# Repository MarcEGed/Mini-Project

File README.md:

# FELCOM

FELCOM is a secure handheld communication device built around the ESP32 and nRF24L01+. The firmware supports frequency-hopping communication, text chat, voice, synchronization, and RF testing.

## Repository layout

- [`FELCOM/`](FELCOM/) - PlatformIO firmware project.
- [`hardware/`](hardware/) - KiCad PCB design, fabrication outputs, and hardware images.
- [`docs/`](docs/) - Project notes, report sources and deliverables, diagrams, and hardware documentation.
- [`miscExperimenting/`](miscExperimenting/) - Earlier Arduino sketches and communication experiments.
- [`template/`](template/) - Typst report template and license.

## Documentation

- [`docs/felcom/AUDIO.md`](docs/felcom/AUDIO.md) - Audio pipeline, wiring, FEC behavior, and troubleshooting.
- [`docs/felcom/fhss.md`](docs/felcom/fhss.md) - FHSS channels, packet format, and synchronization design.
- [`docs/hardware/README.md`](docs/hardware/README.md) - Circuit assembly references.
- [`docs/report/`](docs/report/) - Typst report source, PDF report, and presentation.
- [`docs/diagrams/`](docs/diagrams/) - Mermaid source files and rendered report diagrams.

## Build and upload

Install PlatformIO, connect an ESP32 development board, and run the commands from `FELCOM/`:

```sh
pio run -e esp32dev
pio run -e esp32dev -t upload
```

The two communicating boards must run the same firmware. Use the Sync Test screen to synchronize their hopping schedule before using chat or audio.

## Hardware

The main hardware design is in [`hardware/fabrication_pcb/`](hardware/fabrication_pcb/). Consult the hardware documentation before assembling a board. Pin assignments and firmware configuration are in [`FELCOM/include/config.h`](FELCOM/include/config.h).

## Report

The current report and presentation are available in [`docs/report/`](docs/report/). The report source is compiled with Typst and uses the diagrams in [`docs/diagrams/`](docs/diagrams/) and images in [`hardware/imgs/`](hardware/imgs/).

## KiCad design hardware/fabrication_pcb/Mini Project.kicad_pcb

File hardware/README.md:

# Reference For Circuit Assembly

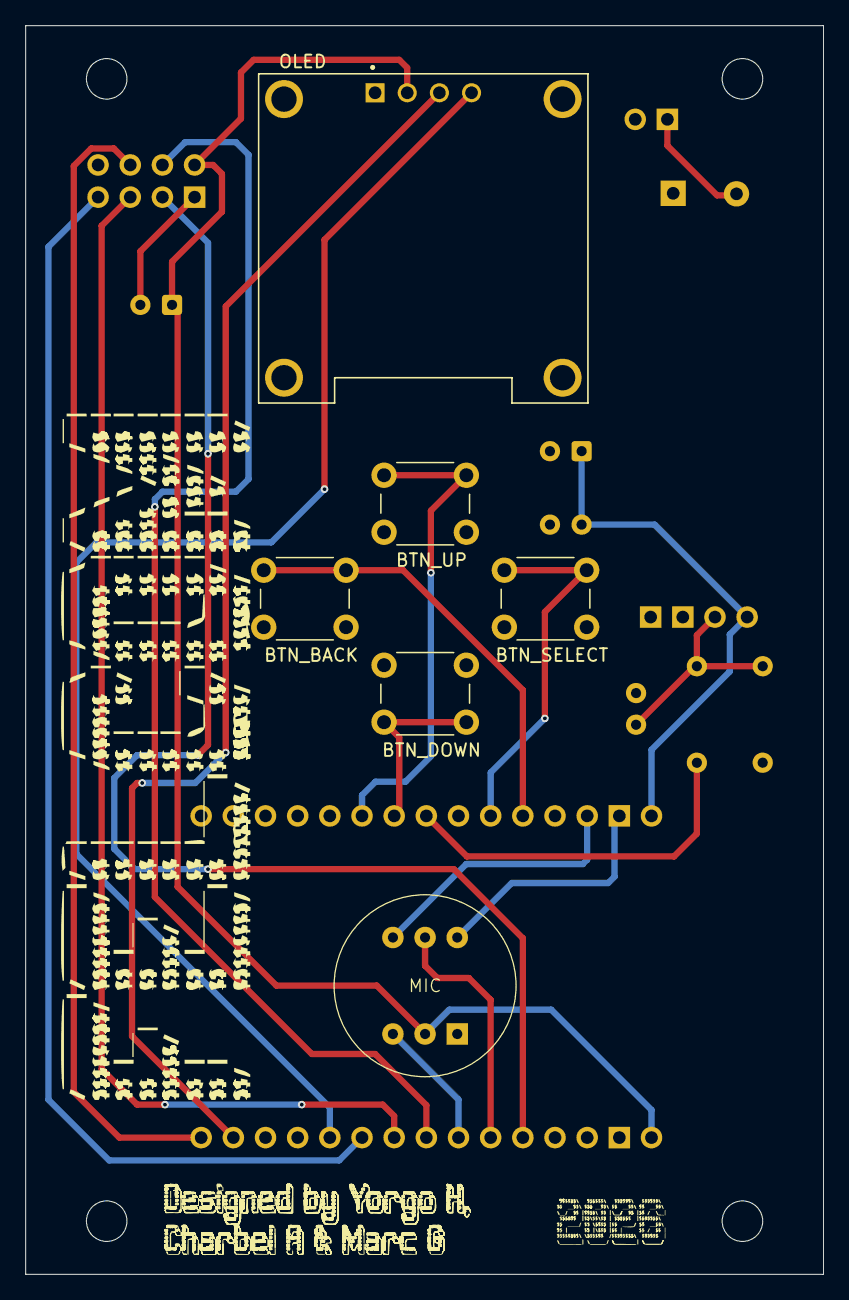
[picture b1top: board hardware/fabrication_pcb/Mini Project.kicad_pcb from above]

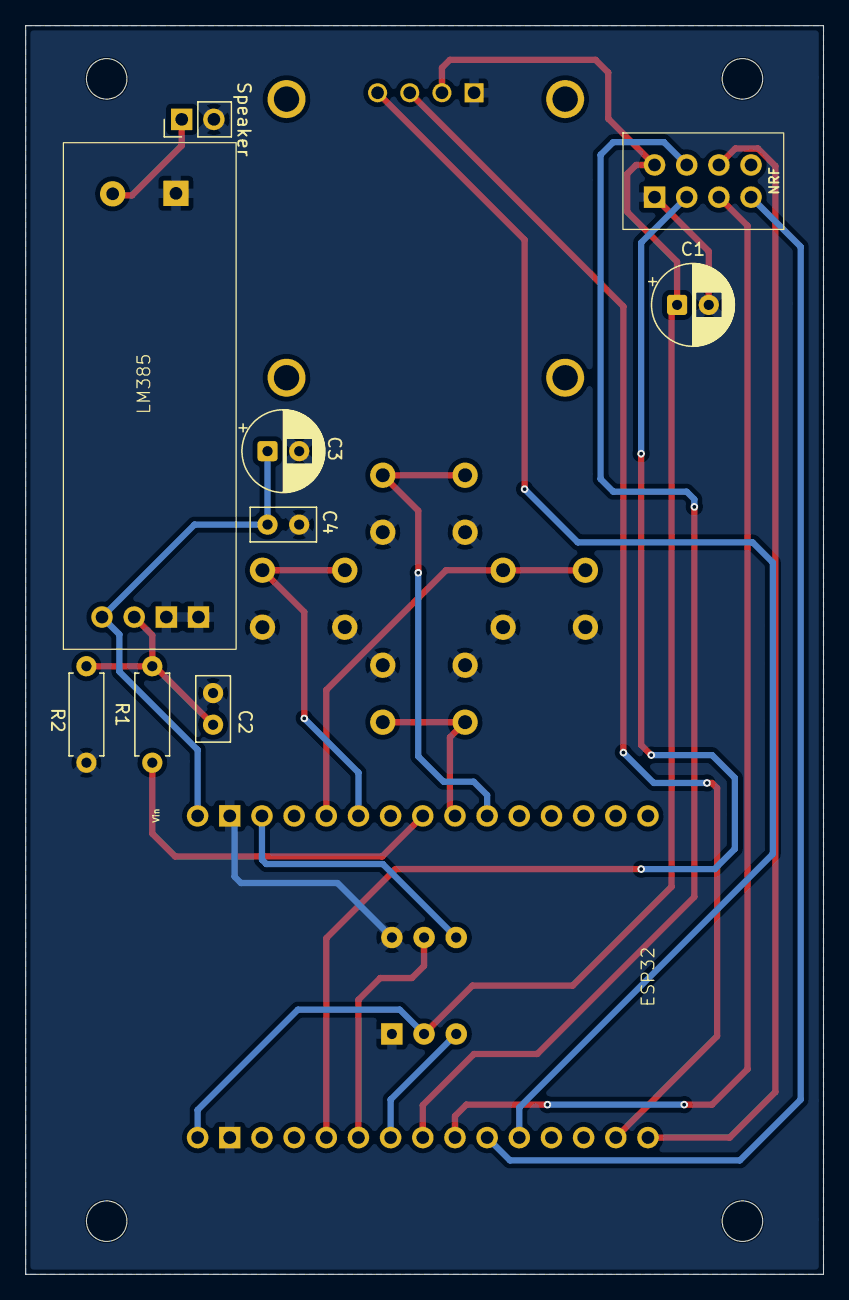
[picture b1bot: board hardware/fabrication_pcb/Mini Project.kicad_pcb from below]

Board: 2 copper layers, 63.0 x 98.6 mm, 20 parts (10 on the bottom side), 20 nets.

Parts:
C1, C3: 47uF; CP_Radial_D6.3mm_P2.50mm
C2, C4: 100nF; C_Disc_D5.0mm_W2.5mm_P2.50mm
ESP32: ESP32_DevKit_V1_30pin
H1, H2, H3, H4: MountingHole; MountingHole_3.2mm_M3
J1: Speaker; PinHeader_1x02_P2.54mm_Vertical
LM385: AMP; LM386_MODULE
MIC: MIC; MH-ET_I2S_MICROPHONE_MODULE
OLED : OLED Display; MODULE_DM-OLED096-636
R1: 10K; R_Axial_DIN0207_L6.3mm_D2.5mm_P7.62mm_Horizontal
R2: 1K; R_Axial_DIN0207_L6.3mm_D2.5mm_P7.62mm_Horizontal
S1: BTN_UP; SW_PUSH_6mm
S2: BTN_DOWN; SW_PUSH_6mm
S3: BTN_SELECT; SW_PUSH_6mm
S4: BTN_BACK; SW_PUSH_6mm
nrf1: NRF24L01_PA_LNA

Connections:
+3.3V: C1.1, ESP32.1 (3V3), MIC.2 (VCC), OLED.2 (VCC), nrf1.2 (VCC)
+5V: C3.1, C4.1, ESP32.16 (VIN), LM385.1 (VCC)
BTN_BACK: ESP32.20 (D14), S4.1
BTN_DOWN: ESP32.24 (D33), S2.2
BTN_SELECT: ESP32.21 (D27), S3.1
BTN_UP: ESP32.25 (D32), S1.1
CE: ESP32.5 (D4), nrf1.3 (CE)
CSN: ESP32.8 (D5), nrf1.4 (CSN)
GND: C1.2, C2.2, C3.2, C4.2, ESP32.2 (GND), ESP32.17 (GND), J1.2, LM385.3 (GND), LM385.4 (GND), LM385.6 (GND), MIC.3 (GND), MIC.4 (L/R), OLED.1 (GND), R2.2, S1.2, S2.1, S3.2, S4.2, nrf1.1 (GND)
MISO: ESP32.10 (D19), nrf1.7 (MISO)
MOSI: ESP32.15 (D23), nrf1.6 (MOSI)
unnamed: J1.1, LM385.5 (OUT)
unnamed: C2.1, LM385.2 (IN), R1.2, R2.1
SCK: ESP32.9 (D18), nrf1.5 (SCK)
SCK_M: ESP32.18 (D13), MIC.6 (SCK)
SCL: ESP32.14 (D22), OLED.3 (SCK)
SD: ESP32.7 (D17), MIC.1 (SD)
SDA: ESP32.11 (D21), OLED.4 (SDA)
WS: ESP32.6 (D16), MIC.5 (WS)
dac_out: ESP32.23 (D25), R1.1

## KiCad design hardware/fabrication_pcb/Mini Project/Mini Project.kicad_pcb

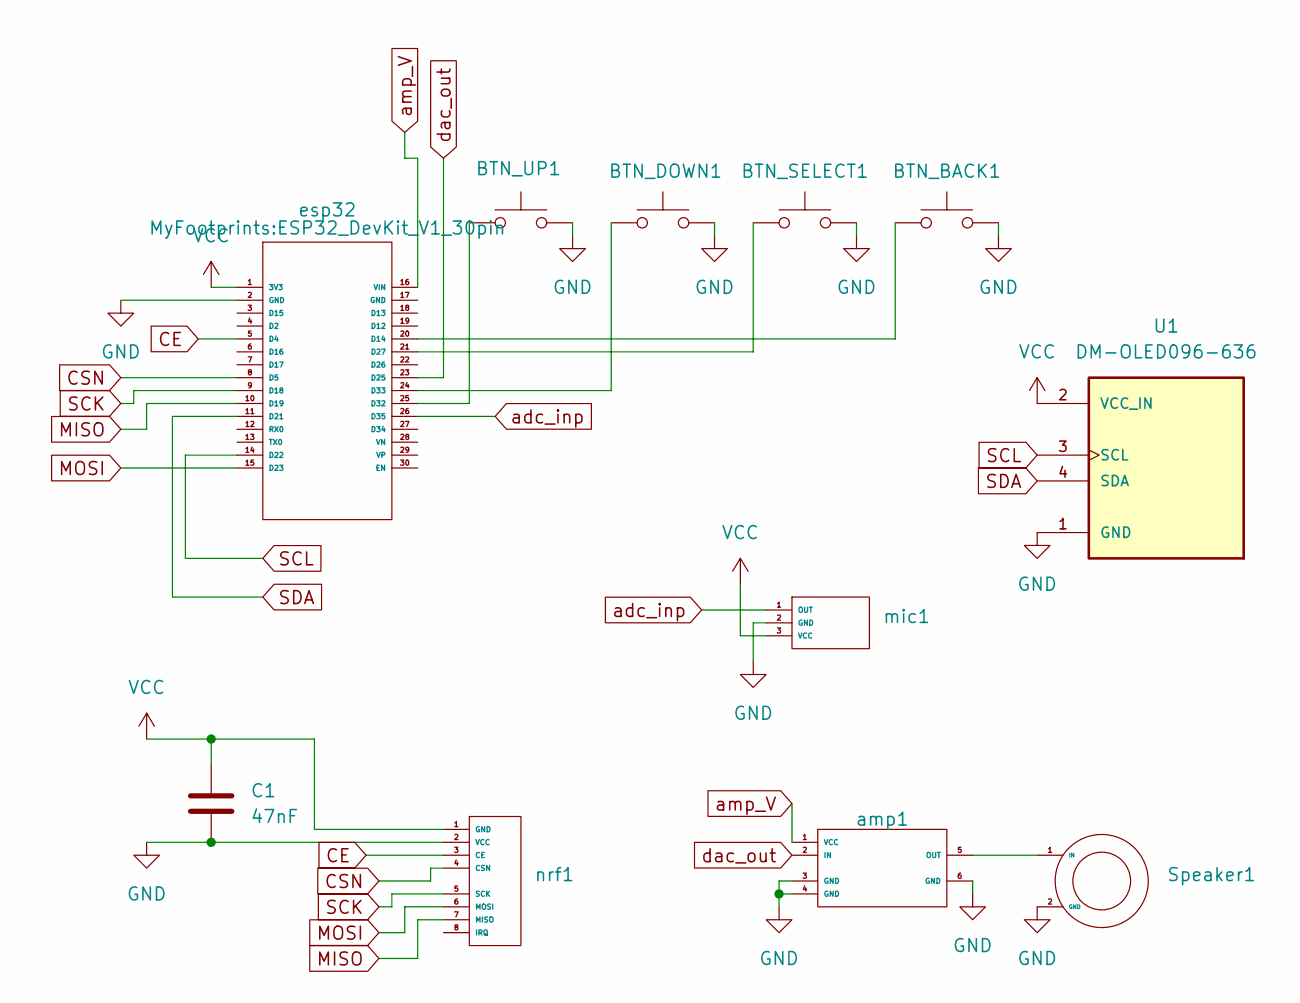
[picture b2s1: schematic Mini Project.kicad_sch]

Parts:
BTN_BACK1: SW_Push; SW_PUSH_6mm
BTN_DOWN1: SW_Push; SW_PUSH_6mm
BTN_SELECT1: SW_Push; SW_PUSH_6mm
BTN_UP1: SW_Push; SW_PUSH_6mm
C1: 47nF; CP_Radial_D6.3mm_P2.50mm
Speaker1: 0.25W_8OHM_SPEAKER
U1: DM-OLED096-636; MODULE_DM-OLED096-636; PARTREV 2018-09-10
amp1: LM386_MODULE
esp32: ESP32_DevKit_V1_30pin
mic1: MAX4466_MODULE
nrf1: NRF24L01_PA_LNA

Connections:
CE: esp32.5 (D4), nrf1.3 (CE)
CSN: esp32.8 (D5), nrf1.4 (CSN)
GND: BTN_BACK1.2, BTN_DOWN1.2, BTN_SELECT1.2, BTN_UP1.2, C1.2, Speaker1.2 (GND), U1.1 (GND), amp1.3 (GND), amp1.4 (GND), amp1.6 (GND), esp32.2 (GND), mic1.2 (GND), nrf1.2 (VCC)
MISO: esp32.10 (D19), nrf1.7 (MISO)
MOSI: esp32.15 (D23), nrf1.6 (MOSI)
unnamed: Speaker1.1 (IN), amp1.5 (OUT)
unnamed: BTN_BACK1.1, esp32.20 (D14)
unnamed: BTN_SELECT1.1, esp32.21 (D27)
unnamed: BTN_UP1.1, esp32.25 (D32)
unnamed: BTN_DOWN1.1, esp32.24 (D33)
SCK: esp32.9 (D18), nrf1.5 (SCK)
SCL: U1.3 (SCL), esp32.14 (D22)
SDA: U1.4 (SDA), esp32.11 (D21)
VCC: C1.1, U1.2 (VCC_IN), esp32.1 (3V3), mic1.3 (VCC), nrf1.1 (GND)
adc_inp: esp32.26 (D35), mic1.1 (OUT)
amp_V: amp1.1 (VCC), esp32.16 (VIN)
dac_out: amp1.2 (IN), esp32.23 (D25)

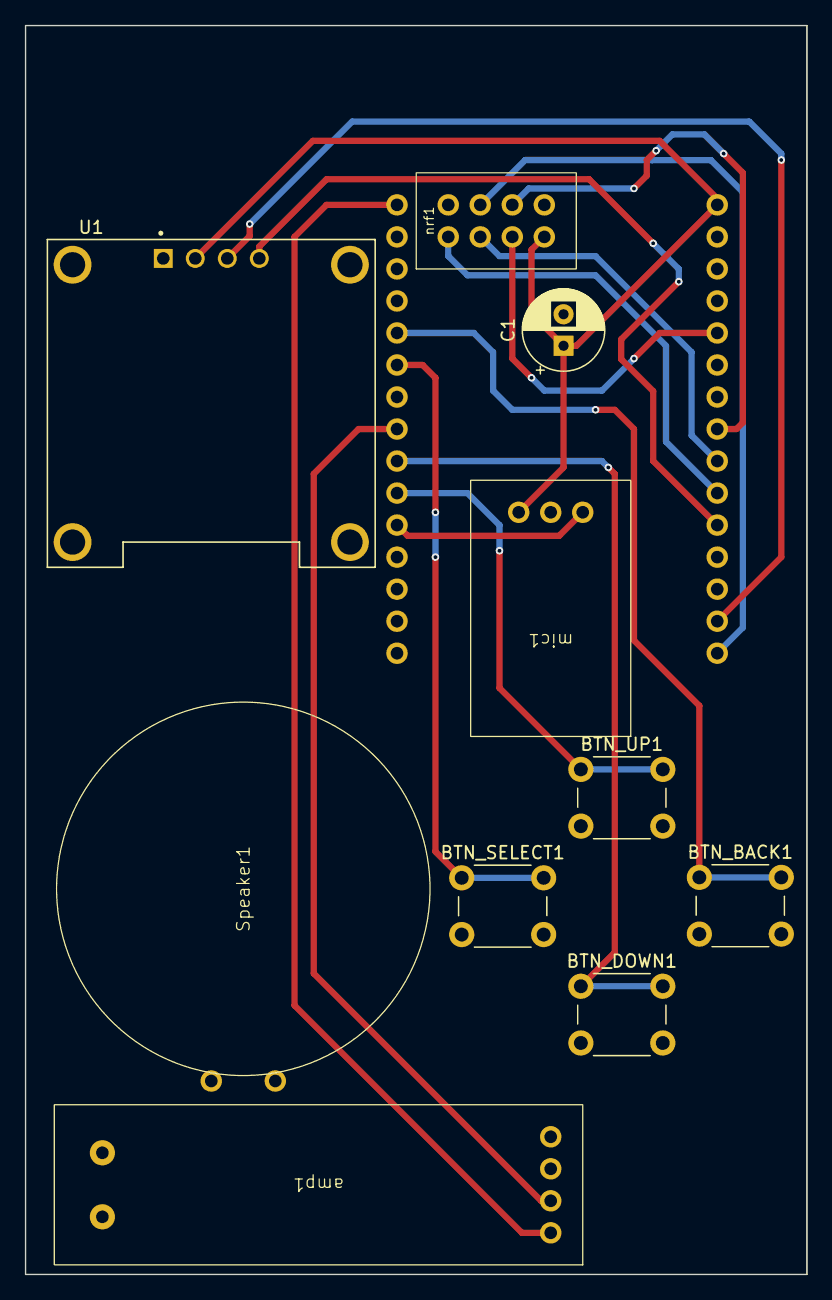
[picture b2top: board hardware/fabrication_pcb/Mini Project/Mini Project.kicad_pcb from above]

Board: 2 copper layers, 62.0 x 99.1 mm, 11 parts (1 on the bottom side), 17 nets.

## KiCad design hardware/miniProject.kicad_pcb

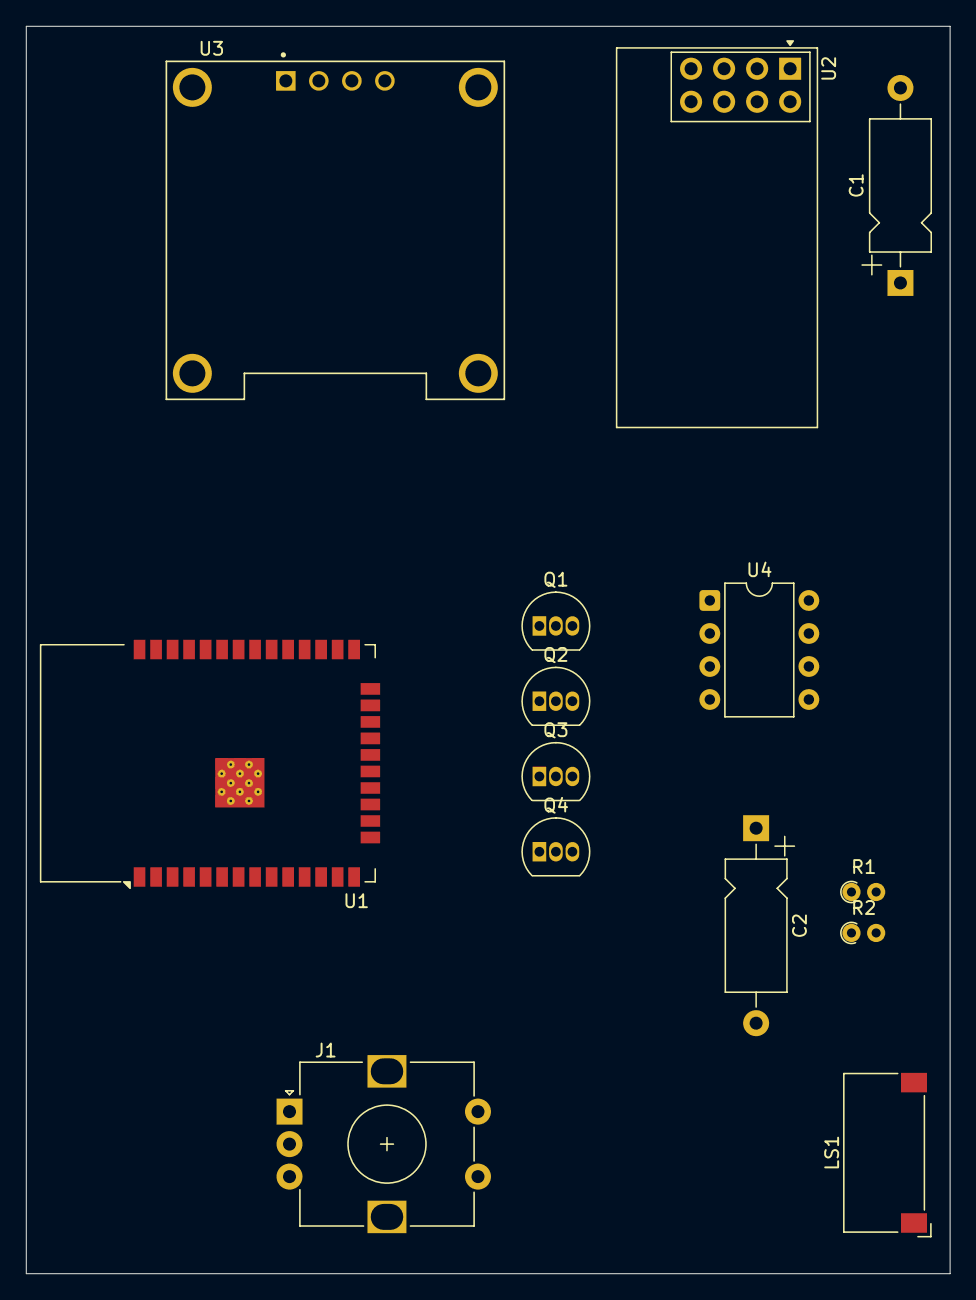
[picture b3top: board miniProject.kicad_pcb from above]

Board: 2 copper layers, 71.1 x 96.0 mm, 14 parts (0 on the bottom side), 17 nets, no tracks yet.

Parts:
C1: 47uF; CP_Axial_L10.0mm_D4.5mm_P15.00mm_Horizontal
C2: 100uF; CP_Axial_L10.0mm_D4.5mm_P15.00mm_Horizontal
J1: ENCODER; RotaryEncoder_Alps_EC12E-Switch_Vertical_H20mm
LS1: Speaker 0.25W 8Ohm; Speaker_CUI_CMR-1206S-67
Q1, Q2: 2n2222; TO-92_Inline
Q3, Q4: BC327; TO-92_Inline
R1: 10K; R_Axial_DIN0204_L3.6mm_D1.6mm_P1.90mm_Vertical
R2: 20K; R_Axial_DIN0204_L3.6mm_D1.6mm_P1.90mm_Vertical
U1: ESP32-WROOM-32E; ESP32-WROOM-32D
U2: NRF24L01; nRF24L01_Breakout
U3: OLED SCREEN; MODULE_DM-OLED096-636
U4: LM358; DIP-8_W7.62mm

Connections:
+9V: Q1.1 (C), Q2.1 (C), U4.8 (V+)
CE: U1.26 (IO4), U2.3 (CE)
CSN: U1.29 (IO5), U2.4 (~CSN)
GND: C1.2, LS1.2, Q3.1 (C), Q4.1 (C), R1.2, U1.1 (GND), U1.15 (GND), U1.38 (GND), U1.39 (GND), U2.1 (GND), U3.1 (GND), U4.4 (V-)
MISO: U1.31 (IO19), U2.7 (MISO)
MOSI: U1.37 (IO23), U2.6 (MOSI)
unnamed: C2.2, LS1.1
unnamed: Q1.2 (B), Q3.2 (B), R2.2, U4.1
unnamed: Q1.3 (E), Q2.2 (B)
unnamed: C2.1, Q2.3 (E), Q4.3 (E)
unnamed: Q3.3 (E), Q4.2 (B)
unnamed: U1.25 (IO0), U4.3 (+)
unnamed: U1.33 (IO21), U3.4 (SDA)
unnamed: U1.36 (IO22), U3.3 (SCL)
unnamed: R1.1, R2.1, U4.2 (-)
SCK: U1.30 (IO18), U2.5 (SCK)
VDD: C1.1, U1.2 (VDD), U2.2 (VCC), U3.2 (VCC_IN)

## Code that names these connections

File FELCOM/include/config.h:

#ifndef CONFIG_H
#define CONFIG_H
#include <stdint.h>

// NODE config
#ifndef FELCOM_VERSION
#define FELCOM_VERSION "unknown"
#endif
// change for each device flashed
#ifndef NODE_ID
#define NODE_ID 'B'
#endif

// Debug config
#define DEBUG 1
#define DEBUG_SERIAL Serial
#define DEBUG_BAUD 9600

// Interference Testing Mode
#define TEST_PATTERN 0xAB
#define RF_TEST_PACKET_SIZE 28
#define RF_TEST_DELAY_MS 1000

// NRF24L01 config
#define NRF24L01_CE_PIN 4
#define NRF24L01_CSN_PIN 5
#define NRF24L01_POWER_LEVEL RF24_PA_MAX
#define NRF24L01_DATA_RATE RF24_1MBPS
// nodes needs to be on the same PHY to talk to each other
// MAX 5
#define NRF24L01_PHY_ADDR 0
// ADDR 0 and 1 will store a full 5-byte address.
// ADDR 2-5 will technically only store a single byte, borrowing up to 4
// additional bytes from pipe 1 per the assigned address width
const uint8_t PHY_ADDRESSES[6][6] = {"FELCO", "GELCO", "HELCO",
                                     "JELCO", "KELCO", "LELCO"};

#define HOPPING_CHANNELS_SIZE 6
const uint8_t HOPPING_CHANNELS[HOPPING_CHANNELS_SIZE] = {110, 111, 112,
                                                         113, 114, 115};

// Chat Config
// Shrunk from 25/22 so the chat wire frame (2B seq + msg + 2B CRC) fits the
// 28-byte data[] region once the FEC layer reserves seq + CRC. See fec.md.
#define MAX_INPUT_LENGTH 18
#define LOG_SIZE 10
#define MSG_MAX_TEXT 18

// Encryption Config
#define XOR_KEY {0xBB, 0x7A, 0x67, 0x99}
#define XOR_KEY_LEN 4

// button inputs
#define BTN_UP_PIN 32
#define BTN_DOWN_PIN 33
#define BTN_SELECT_PIN 27
#define BTN_BACK_PIN 14


// Screen config
#define I2C_ADDR 0x3C
#define SCREEN_WIDTH 128
#define SCREEN_HEIGHT 64
#define SCREEN_SDA_PIN 21
#define SCREEN_SCL_PIN 22

// INMP441 I2S Microphone
#define I2S_PORT I2S_NUM_0
#define I2S_SCK_PIN 13  // Serial clock
#define I2S_WS_PIN 16   // Word select
#define I2S_SD_PIN 17   // Serial data in
// L/R: wire to GND on module, no GPIO needed

// DAC output (receiver side only)
#define DAC_OUT_PIN 25  // ESP32 DAC1 (GPIO25) — matches the audio amp wiring

// Audio config
#define AUDIO_SAMPLE_RATE 8000   // Hz
#define AUDIO_PACKET_SAMPLES 24  // seq(2) + samples(24) = 26 user bytes (FEC_AUDIO_SAMPLES)
// 0 = disabled, 1 = TX (mic), 2 = RX (speaker), 3 = both if ever needed
#define AUDIO_ENABLED 1
// INMP441 L/R tied to GND selects the left I2S slot. With ESP32 legacy I2S in
// RIGHT_LEFT mode, boards/libraries can disagree on whether that arrives as
// buffer index 0 or 1. If mic diagnostics show near-zero level, try changing
// this between 0 and 1 before changing gain.
#define AUDIO_I2S_SLOT_INDEX 0
// Software mic gain: scaled = (centered * AUDIO_GAIN) >> 16.
//   higher = louder but more clipping/hiss; lower = cleaner but quieter.
//   Tune by ear: try 12 / 18 / 24 / 32.
#define AUDIO_GAIN 8
// Set to 1 to hear locally the same 8-bit mic samples being transmitted while
// TALKING. Useful for checking mic/I2S/gain before debugging the radio link.
#define AUDIO_LOCAL_MONITOR 0
// Max local monitor backlog while TALKING. Lower = less sidetone delay; if too
// low it can sound rough because old samples are dropped to stay live.
#define AUDIO_LOCAL_MONITOR_MAX_QUEUED 24
// Set to 0 to test only the mic -> local DAC path without nRF24/FEC blocking.
// Leave 1 for normal walkie-talkie TX.
#define AUDIO_RADIO_TX_ENABLE 1
// Set to 1 for serial audio diagnostics. Keep 0 for normal playback: serial
// printing stalls the cooperative audio loop and causes audible glitches.
#define AUDIO_SERIAL_DEBUG 0
// DAC playback ring (power of two; smooths radio jitter in LISTEN and paces the
// local mic monitor in TALK).
#define AUDIO_RX_RING 4096

// FEC config — see "FEC Prototype — Design Document" (fec.md)
#define FEC_XOR_BLOCK_SIZE 4    // data packets per XOR block (+1 parity packet)
#define FEC_ARQ_TIMEOUT_MS 200  // wait for ACK before retransmit
#define FEC_ARQ_MAX_RETRIES 3   // max ARQ retransmissions
#define FEC_AUDIO_RX_QUEUE 8    // recovered audio payloads buffered for playback

// Pong config
#define PONG_SCORE_TO_WIN 7
#define PONG_TICK_MS 30
#define PONG_TX_INTERVAL_MS 15

#endif  // CONFIG_H

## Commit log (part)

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2026-03-03 added placeholders
2026-03-05 feat: use platformIO file structure
2026-03-06 Initial commit: NRF + ESP32 testing code
2026-03-06 Added ESP32 NRF testing code
2026-03-18 feat: add scaffolding for display, pong, and start with NRF24
2026-03-19 fix: vprint no available in esp, use extern for display
2026-03-19 feat: make display pins configurable
2026-03-19 feat: add rotary encoder, some improvements to pong
2026-03-19 Added kicad schematic for easy assembly
2026-03-19 added README for ease of use
2026-03-20 fixed fuckup
2026-03-20 feat: add transceiver struct
2026-03-20 feat: added joystick option
2026-03-20 doc: my stuff was trippin
2026-03-21 feat!: move drivers to the lib folder
    fix includes in project
    fix functions defined moved to cpp file, heder only contains declaration
2026-03-22 feat\!: UNTESTED MESSAGING ADDED
2026-03-22 feat(untested): added input file
2026-03-22 fix(build success): solved and doc build solution
2026-03-22 feat!: complete messaging draft
2026-03-22 feat!: complete texting (screen bug)
2026-03-22 fix: thrice message issue
2026-03-23 fix: commented out inCaseItBreaks files
2026-03-24 Added speaker circuitry
2026-03-24 fix: minor convenience fixes
2026-03-24 feat: XOR key based encryption
2026-03-24 feat: add documentation about the wireless module
2026-03-24 fix: update docs
2026-03-25 feat: use google style guide
2026-03-25 feat: implement FHSS
2026-03-25 fix: remove unnecessary include from config.h
2026-03-27 test:trying to find fixes
2026-03-29 test: CRC off - no corruption(marc test)
2026-03-29 feat: BER test mode
2026-04-02 fix: BER menu with BER 5% MAX
2026-04-02 feat:added menu
2026-04-02 feat: added pong
2026-04-03 feat: send different frequencies through button
2026-04-03 feat: menus+pong
2026-04-16 feat: add tiny pcb test
2026-04-17 feat: ¯\_(ツ)_/¯
2026-04-17 fix: rcv menu size
2026-04-17 feat: revamp UI and add menu
2026-04-17 fix: update menu on selection don't init, fix typo in enum
2026-04-17 fix: added line in main
2026-04-17 feat: add pong UI, and FELCOM LOGO
2026-04-17 feat: add rf test mode UI
2026-04-22 lowkey have no clue what's going on
2026-04-22 feat: added button controls
2026-04-23 feat: added basic pcb layout
2026-04-23 feat: very bad basic routing
2026-04-24 feat: enable auto acks and retries
2026-04-24 fix: minor pcb stuff
2026-04-29 feat:added button mode
2026-05-01 feat: pcb routing + mic input
2026-05-01 feat: add top bar for menu, generate ID and name on compilation
2026-05-04 feat: added completed pcb - thanks yorgi
2026-05-04 feat: exported gerbers
2026-05-04 update footprints and symbols
2026-05-04 fix: symbols and footprints per project
2026-05-05 feat: updated pcb layout
2026-05-06 fix: schematic looking fancy, component placement done
2026-05-06 feat: routed
2026-05-06 feat: mount holes
2026-05-07 Feat: silkscreen art
2026-05-07 feat: ORDERED PCBgit add .
2026-05-11 feat: minor clenaning schematic
2026-05-11 feat: trying to add audio as menu
2026-05-11 fix: disable fhss, fix formatting and merge artifacts
2026-05-11 fix: pong input direction and continuous input
2026-05-13 feat: add new packet format, use node_id as name too
2026-05-18 feat: packet multiplexing, and CSMA
2026-05-20 feat: implement FHSS using hardware timer and synchronization
2026-05-20 fix: don't like it but I push to test
2026-05-25 feat: reimplementation of ND and network joining
2026-05-29 feat: fhss implementation work, chat display channel and timer
2026-05-29 Test fhss sync, not fully working
2026-05-30 fix: stash conflicts
2026-05-30 feat: remove fhss
2026-06-04 feat: add a counter that gets incremented every 500ms
2026-06-04 feat: add comments on what to do next
2026-06-04 feat: add timing synchronization
2026-06-05 feat: fhss sync working
2026-06-06 feat:fhss works, no audio tested
2026-06-06 feat: add layered FEC inuilt in transceiver
2026-06-06 feat: add FEC print on serial monitor
2026-06-06 feat: real-time audio over FHSS + FEC
2026-06-08 feat: serial debug for microphone
2026-06-08 feat: add uni broadcast screen
2026-06-10 Revert "feat: serial debug for microphone"
    This reverts commit 4fbba1663a749d9e18d29b444c52bfc33913aaa9.
2026-06-11 fix: transmit audio without csma, better dac playback, add local debug
2026-06-25 docs: update fhss.md and fix the report (up to C4)
2026-06-25 fixed + checked rest of report C4-end
2026-06-25 fix: update diagrams and pictures
2026-06-25 docs: add FELCOM picture, open issues section
2026-06-25 qol commit
2026-06-25 docs: update conclusion, open issues and challenges
2026-06-25 docs: small improvements
2026-06-25 docs: ai review gramer
2026-06-26 minor ppt fix and report fix
2026-06-26 docs: report enhancements
2026-06-26 docs: submit
2026-06-29 fix: cleanup before demo, sort menu items
